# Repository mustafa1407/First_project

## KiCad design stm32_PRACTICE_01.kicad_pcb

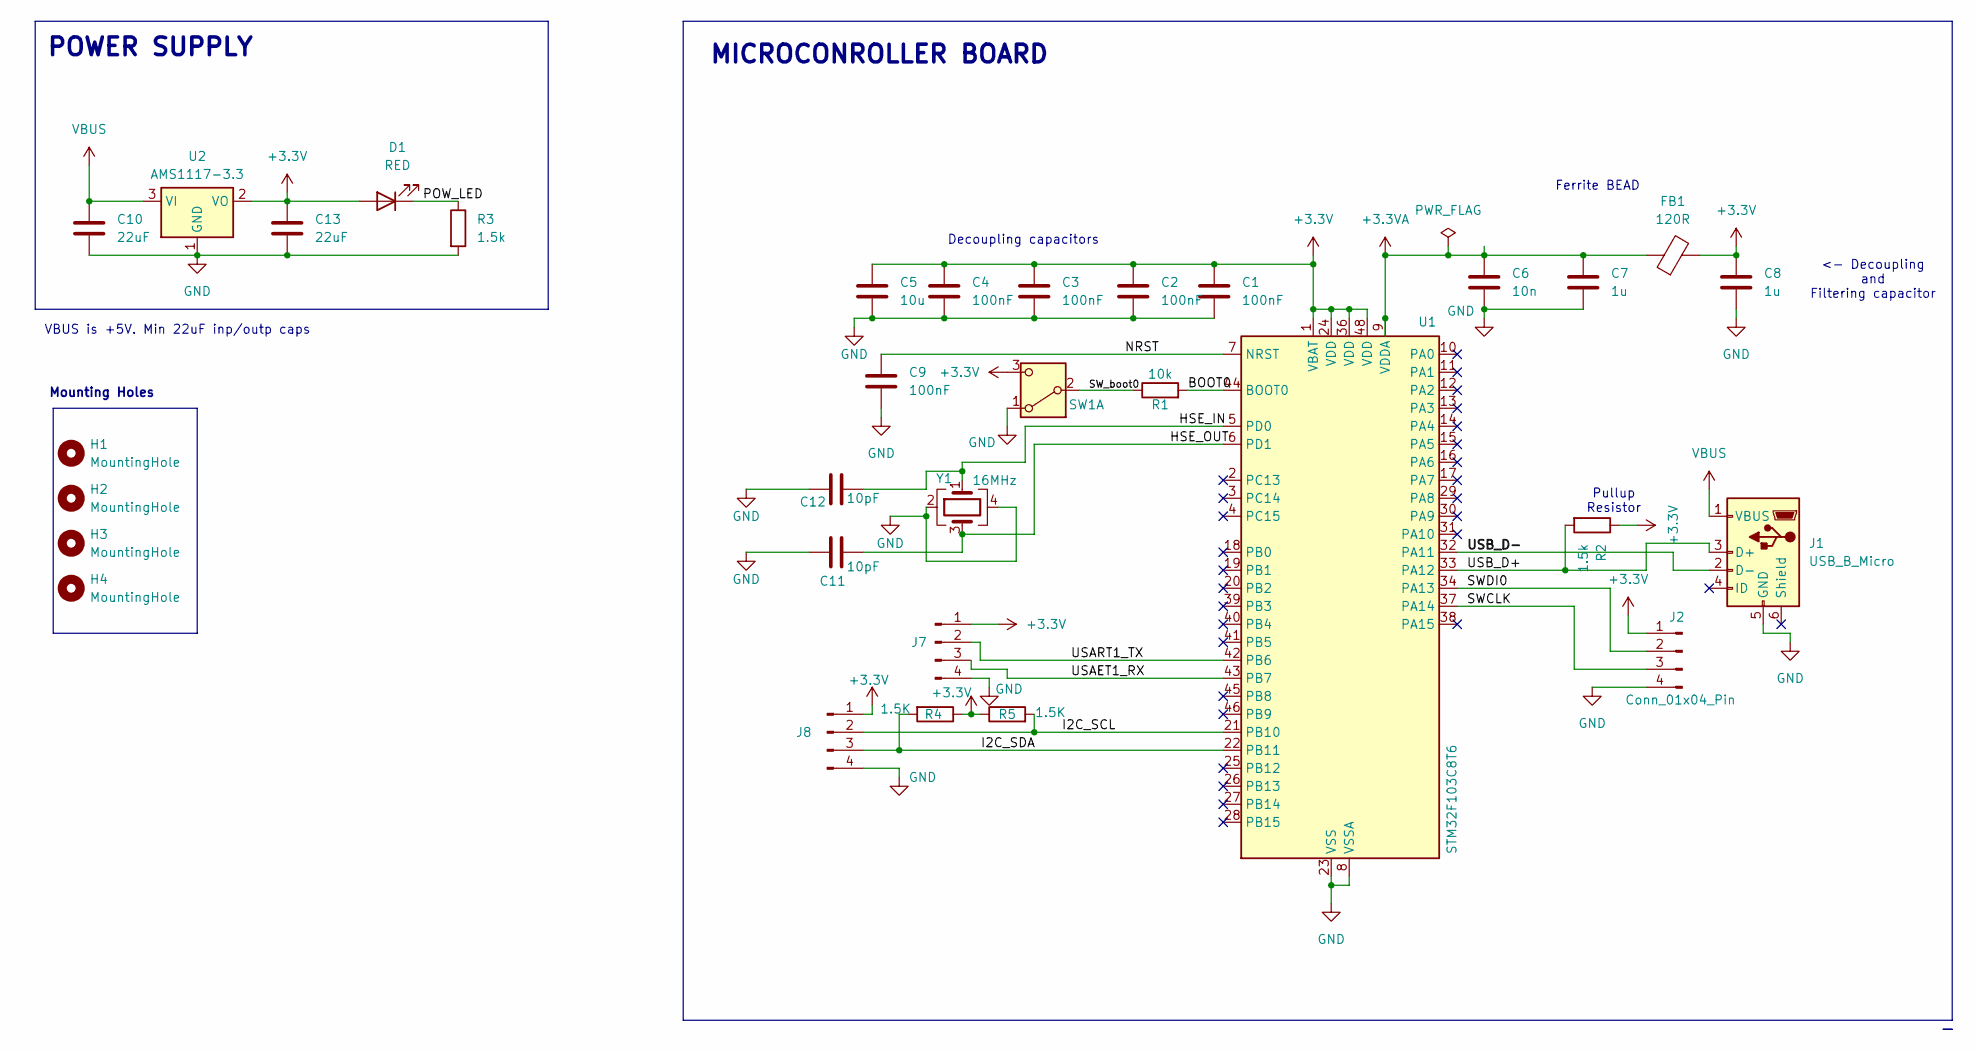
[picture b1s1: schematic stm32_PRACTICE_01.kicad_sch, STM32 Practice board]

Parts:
C1, C2, C3, C4, C9: 100nF; C_0402_1005Metric
C5: 10u; C_0603_1608Metric
C6: 10n; C_0402_1005Metric
C7, C8: 1u; C_0402_1005Metric
C10, C13: 22uF; C_0805_2012Metric
C11, C12: 10pF; C_0402_1005Metric
D1: RED; LED_0603_1608Metric
FB1: 120R; L_0603_1608Metric
H1, H2, H3, H4: MountingHole; MountingHole_2.2mm_M2
J1: USB_B_Micro; USB_Micro-B_Wuerth_629105150521
J2, J7, J8: Conn_01x04_Pin; PinHeader_1x04_P2.54mm_Vertical
R1: 10k; R_0402_1005Metric
R2, R3: 1.5k; R_0402_1005Metric
R4, R5: 1.5K; R_0402_1005Metric
SW1: SW_DPDT_x2; SW_SPDT_PCM12
U1: STM32F103C8T6; LQFP-48_7x7mm_P0.5mm
U2: AMS1117-3.3; SOT-223-3_TabPin2
Y1: 16MHz; Crystal_SMD_3225-4Pin_3.2x2.5mm

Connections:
+3.3V: C1.1, C2.1, C3.1, C4.1, C5.1, C8.1, C13.1, D1.2 (A), FB1.2, J2.1, J7.1, J8.1, R2.1, R4.1, R5.1, SW1.3 (C), U1.1 (VBAT), U1.24 (VDD), U1.36 (VDD), U1.48 (VDD), U2.2 (VO)
+3.3VA: C6.1, C7.1, FB1.1, U1.9 (VDDA)
/BOOT0: R1.2, U1.44 (BOOT0)
/HSE_IN: C12.2, U1.5 (PD0), Y1.1
/HSE_OUT: C11.2, U1.6 (PD1), Y1.3
/I2C_SCL: J8.2, R5.2, U1.21 (PB10)
/I2C_SDA: J8.3, R4.2, U1.22 (PB11)
/NRST: C9.1, U1.7 (NRST)
/POW_LED: D1.1 (K), R3.1
/SWCLK: J2.3, U1.37 (PA14)
/SWDI0: J2.2, U1.34 (PA13)
/SW_boot0: R1.1, SW1.2 (B)
/USAET1_RX: J7.3, U1.43 (PB7)
/USART1_TX: J7.2, U1.42 (PB6)
/USB_D+: J1.3 (D+), R2.2, U1.33 (PA12)
/USB_D-: J1.2 (D-), U1.32 (PA11)
GND: C1.2, C2.2, C3.2, C4.2, C5.2, C6.2, C7.2, C8.2, C9.2, C10.2, C11.1, C12.1, C13.2, J1.5 (GND), J2.4, J7.4, J8.4, R3.2, SW1.1 (A), U1.8 (VSSA), U1.23 (VSS), U1.35 (VSS), U1.47 (VSS), U2.1 (GND), Y1.2, Y1.4
VBUS: C10.1, J1.1 (VBUS), U2.3 (VI)

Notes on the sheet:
Ferrite BEAD
Decoupling capacitors
POWER SUPPLY
<- Decoupling and Filtering capacitor
Mounting Holes
MICROCONROLLER BOARD
VBUS is +5V. Min 22uF inp/outp caps
Pullup Resistor

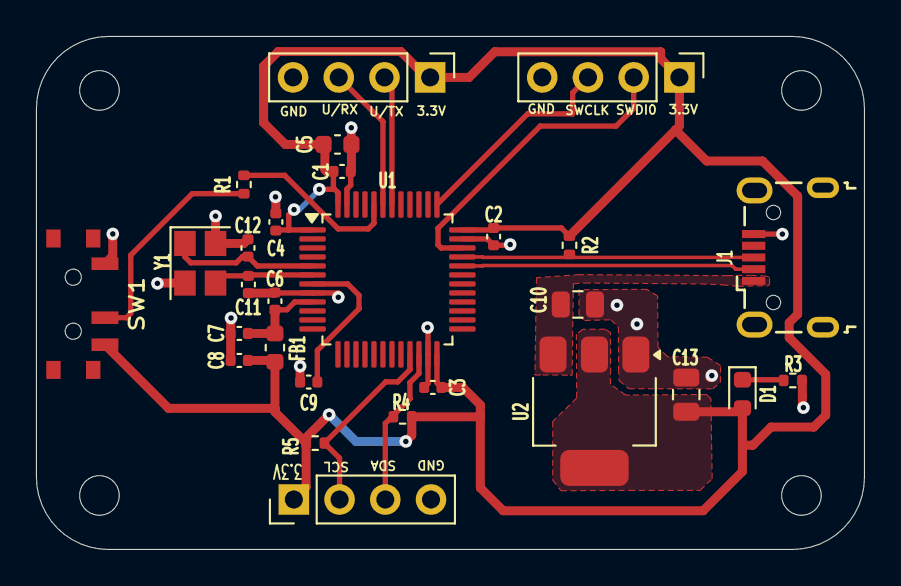
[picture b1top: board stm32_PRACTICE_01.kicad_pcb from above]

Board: 2 copper layers, 46.0 x 28.5 mm, 32 parts (0 on the bottom side), 18 nets.

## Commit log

2024-12-13 STEM
    This is my first KICAD project of STM32. This was made by following youtube video
